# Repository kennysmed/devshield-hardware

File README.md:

devshield-hardware
==================

Schematics and Eagle files for the BERG Cloud Dev Shield.

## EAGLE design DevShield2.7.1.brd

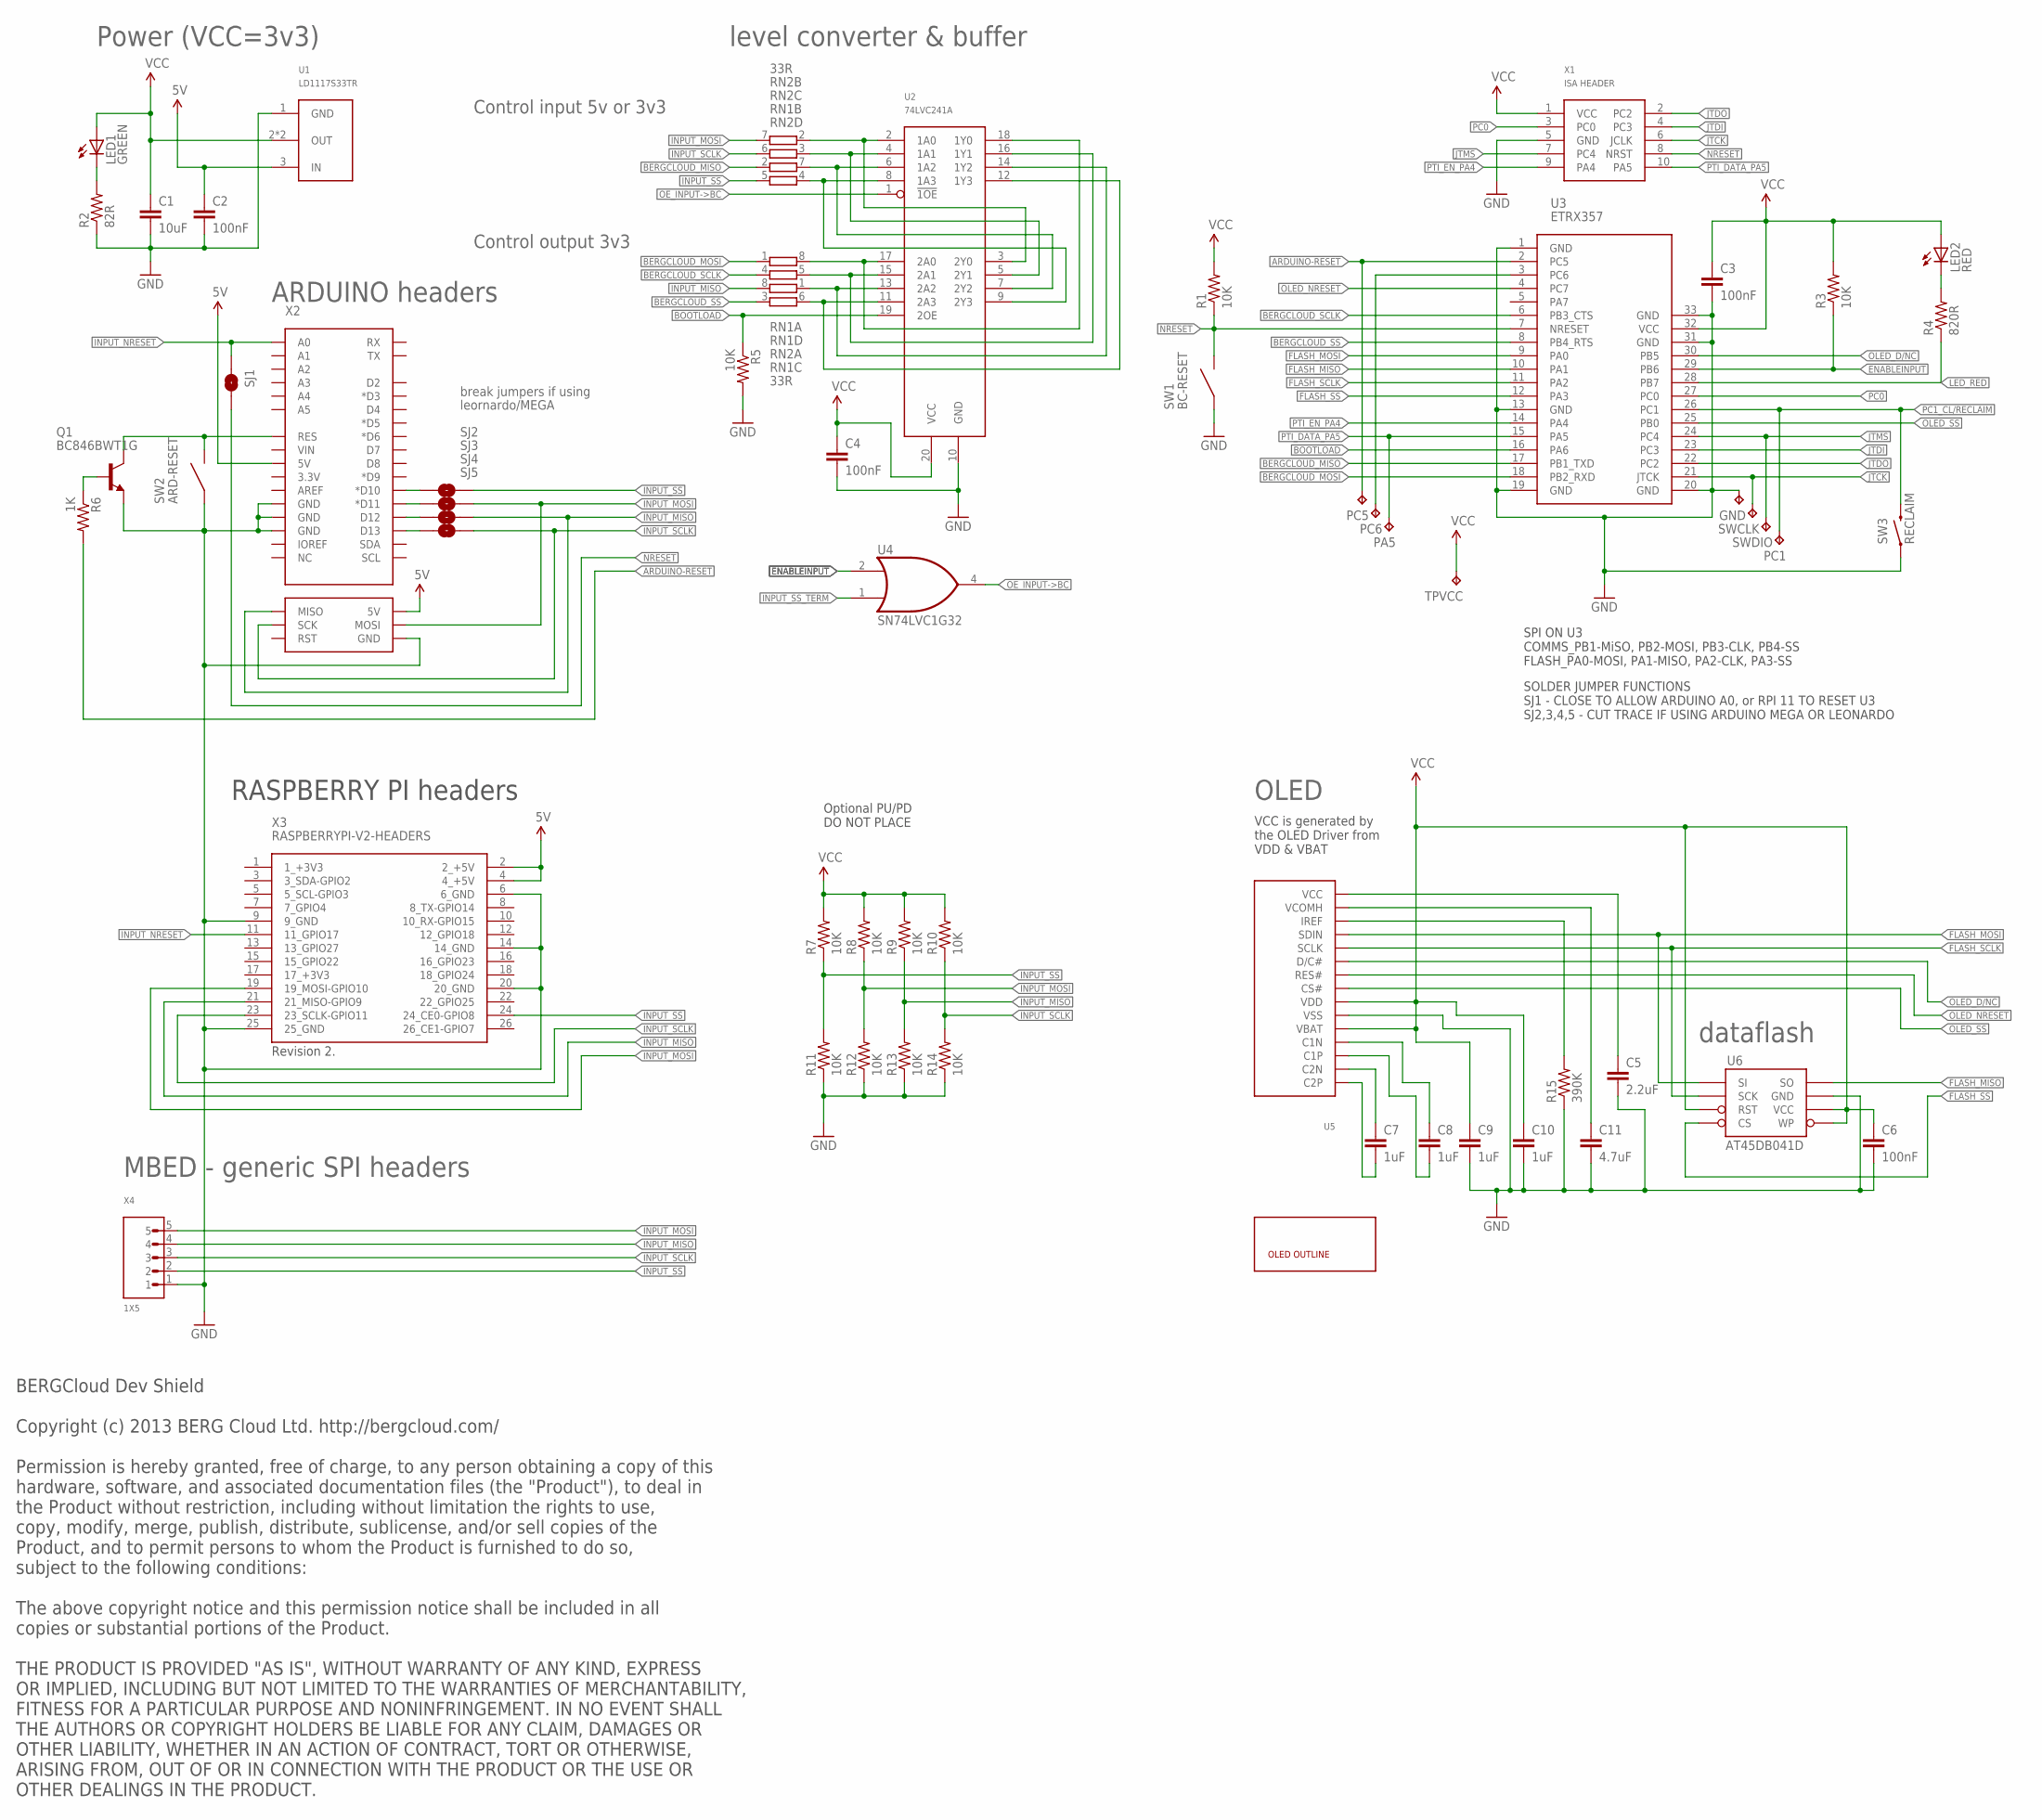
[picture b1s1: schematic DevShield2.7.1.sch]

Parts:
C1: 10uF; C0805K; MPN 06033C104KAZ2A
C2, C3, C4, C6: 100nF; C0603K; MPN 06033C104KAZ2A
C5: 2.2uF; 0603-CAP; MPN 06036D225KAT2A
C7, C8, C9, C10: 1uF; 0603-CAP; MPN 02016D105MAT2A
C11: 4.7uF; 0805; MPN 0805ZD475KAT2A
GND: TPTP15R; TP15R
IGNORE: ER-OLED0.91-1-OUTLINE; ER-OLED0.91-SCREEN
LED1: GREEN; CHIPLED_0603; MPN ASMT-RH45-AQ502
LED2: RED; CHIPLED_0603; MPN ASMT-RH45-AQ502
PA5: TPTP15R; TP15R
PC1, PC5, PC6: TPTP15R; TP15R
Q1: BC846BWT1G; SOT323; MPN BC846BWT1G
R1, R3, R5, R7, R8, R9, R10, R11, R12, R13, R14: 10K; 0603-RES
R2: 82R; 0603-RES
R4: 820R; 0603-RES
R6: 1K; 0603-RES; MPN MC0063W060311K
R15: 390K; 0603-RES; MPN ERJU03F3903V
RN1, RN2: 33R; CAT16
SJ1: SOLDERJUMPERNO; SJ_2S-NO
SJ2, SJ3, SJ4, SJ5: SOLDERJUMPERTRACE; SJ_2S-TRACE
SW1: BC-RESET; TE_FSMSM; MPN FSMSM
SW2: ARD-RESET; TE_FSMSM; MPN FSMSM
SW3: RECLAIM; TACTILE_SWITCH_SMD
SWCLK: TPTP15R; TP15R
SWDIO: TPTP15R; TP15R
TPVCC: TPTP15R; TP15R
U1: LD1117S33TR; SOT223
U2: 74LVC241A; TSSOP20
U3: ETRX357; ETRX35XSMD
U4: SN74LVC1G32; SC70-5; MPN SN74LVC1G32DCKR
U5: ER-OLED0.91-1HANDSOLDER_BOTTOMLAYER; FPC15WAYOLED
U6: AT45DB041D; SO08; MPN AT45DB041D-SSU
X1: ISA HEADER; SHF-105-01-L-D-SM
X2: ARDUINO_UNO_IO_INCL_ICSP; ARDUINO_UNO_ICSP
X3: RASPBERRYPI-V2-HEADERS; 13X2_2.54MM
X4: 1X5; 1X05

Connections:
5V: C2.1, U1.3 (IN), X2.5V@0 (5V), X2.ICSP_5V (5V), X3.2 (2_+5V), X3.4 (4_+5V)
ARDUINO-RESET: PC5.TP, R6.2, U3.2 (PC5)
ARD_RESET_5V: Q1.3 (C), SW2.P$1, X2.RES
BERGCLOUD_MISO: RN1.2 (1), U3.17 (PB1_TXD)
BERGCLOUD_MISO_TERM: RN1.7 (2), U2.6 (1A2), U2.7 (2Y2)
BERGCLOUD_MOSI: RN1.1, U3.18 (PB2_RXD)
BERGCLOUD_MOSI_TERM: RN1.8 (2), U2.17 (2A0), U2.18 (1Y0)
BERGCLOUD_SCLK: RN1.4 (1), U3.6 (PB3_CTS)
BERGCLOUD_SCLK_TERM: RN1.5 (2), U2.15 (2A1), U2.16 (1Y1)
BERGCLOUD_SS: RN1.3 (1), U3.8 (PB4_RTS)
BERGCLOUD_SS_TERM: RN1.6 (2), U2.11 (2A3), U2.12 (1Y3)
BOOTLOAD: R5.1, U2.19 (2OE), U3.16 (PA6)
ENABLEINPUT: R3.1, U3.29 (PB6), U4.2 (I0)
FLASH_MISO: U3.10 (PA1), U6.8 (SO)
FLASH_MOSI: U3.9 (PA0), U5.P$12 (SDIN), U6.1 (SI)
FLASH_SCLK: U3.11 (PA2), U5.P$11 (SCLK), U6.2 (SCK)
FLASH_SS: U3.12 (PA3), U6.4 (CS)
GND: C1.2, C2.2, C3.2, C4.2, C5.2, C6.2, C9.2, C10.2, C11.2, GND.TP, Q1.2 (E), R2.1, R5.2, R11.1, R12.1, R13.1, R14.1, R15.1, SW1.P$2, SW2.P$2, SW3.1, U1.1 (GND), U2.10 (GND), U3.1 (GND), U3.13 (GND), U3.19 (GND), U3.20 (GND), U3.31 (GND), U3.33 (GND), U4.3 (GND), U5.P$6 (VSS), U6.7 (GND), X1.5 (GND), X2.GND@0 (GND), X2.GND@1 (GND), X2.GND@2 (GND), X2.GND@03 (GND), X3.6 (6_GND), X3.9 (9_GND), X3.14 (14_GND), X3.20 (20_GND), X3.25 (25_GND), X4.1
INPUT_MISO: R9.1, R13.2, RN2.8 (2), SJ4.2, X2.ICSP_MISO (MISO), X3.21 (21_MISO-GPIO9), X4.4
INPUT_MISO_TERM: RN2.1, U2.13 (2A2), U2.14 (1Y2)
INPUT_MOSI: R8.1, R12.2, RN2.7 (2), SJ3.2, X2.ICSP_MOSI (MOSI), X3.19 (19_MOSI-GPIO10), X4.5
INPUT_MOSI_TERM: RN2.2 (1), U2.2 (1A0), U2.3 (2Y0)
INPUT_NRESET: SJ1.1, X2.A0, X3.11 (11_GPIO17)
INPUT_SCLK: R10.1, R14.2, RN2.6 (2), SJ5.2, X2.ICSP_SCK (SCK), X3.23 (23_SCLK-GPIO11), X4.3
INPUT_SCLK_TERM: RN2.3 (1), U2.4 (1A1), U2.5 (2Y1)
INPUT_SS: R7.1, R11.2, RN2.5 (2), SJ2.2, X3.24 (24_CE0-GPIO8), X4.2
INPUT_SS_TERM: RN2.4 (1), U2.8 (1A3), U2.9 (2Y3), U4.1 (I1)
JTCK: SWCLK.TP, U3.21 (JTCK), X1.6 (JCLK)
JTDI: U3.23 (PC3), X1.4 (PC3)
JTDO: U3.22 (PC2), X1.2 (PC2)
JTMS: SWDIO.TP, U3.24 (PC4), X1.7 (PC4)
LED_RED: R4.1, U3.28 (PB7)
unnamed: LED1.C, R2.2
unnamed: SJ2.1, X2.D10 (*D10)
unnamed: SJ3.1, X2.D11 (*D11)
unnamed: SJ4.1, X2.D12
unnamed: SJ5.1, X2.D13
unnamed: C7.1, U5.P$2 (C2N)
unnamed: C7.2, U5.P$1 (C2P)
unnamed: C8.2, U5.P$3 (C1P)
unnamed: LED2.C, R4.2
unnamed: C8.1, U5.P$4 (C1N)
unnamed: C5.1, U5.P$15 (VCC)
unnamed: C11.1, U5.P$14 (VCOMH)
unnamed: R15.2, U5.P$13 (IREF)
unnamed: Q1.1 (B), R6.1
NRESET: R1.1, SJ1.2, SW1.P$1, U3.7 (NRESET), X1.8 (NRST)
OE_INPUT->BC: U2.1 (!1OE), U4.4 (O)
OLED_D/NC: U3.30 (PB5), U5.P$10 (D/C#)
OLED_NRESET: U3.4 (PC7), U5.P$9 (RES#)
OLED_SS: U3.25 (PB0), U5.P$8 (CS#)
PC0: U3.27 (PC0), X1.3 (PC0)
PC1_CL/RECLAIM: PC1.TP, SW3.3 (2), U3.26 (PC1)
PC6: PC6.TP, U3.3 (PC6)
PTI_DATA_PA5: PA5.TP, U3.15 (PA5), X1.10 (PA5)
PTI_EN_PA4: U3.14 (PA4), X1.9 (PA4)
VCC: C1.1, C3.1, C4.1, C6.1, C9.1, C10.1, LED1.A, LED2.A, R1.2, R3.2, R7.2, R8.2, R9.2, R10.2, TPVCC.TP, U1.2 (OUT), U1.4 (OUT), U2.20 (VCC), U3.32 (VCC), U4.5 (VCC), U5.P$5 (VBAT), U5.P$7 (VDD), U6.3 (RST), U6.5 (WP), U6.6 (VCC), X1.1 (VCC)

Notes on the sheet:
RASPBERRY PI headers
Control input 5v or 3v3
Control output 3v3
ARDUINO headers
level converter & buffer
break jumpers if using
MBED - generic SPI headers
Power (VCC=3v3)
leornardo/MEGA
dataflash
OLED
VCC is generated by the OLED Driver from VDD & VBAT
SPI ON U3 COMMS_PB1-MiSO, PB2-MOSI, PB3-CLK, PB4-SS FLASH_PA0-MOSI, PA1-MISO, PA2-CLK, PA3-SS
SOLDER JUMPER FUNCTIONS SJ1 - CLOSE TO ALLOW ARDUINO A0, or RPI 11 TO RESET U3 SJ2,3,4,5 - CUT TRACE IF USING ARDUINO MEGA OR LEONARDO
Optional PU/PD DO NOT PLACE
BERGCloud Dev Shield Copyright (c) 2013 BERG Cloud Ltd. http://bergcloud.com/ Permission is hereby granted, free of charge, to any person obtaining a copy of this hardware, software, and associated documentation files (the "Product"), to deal in the Product without restriction, including without li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

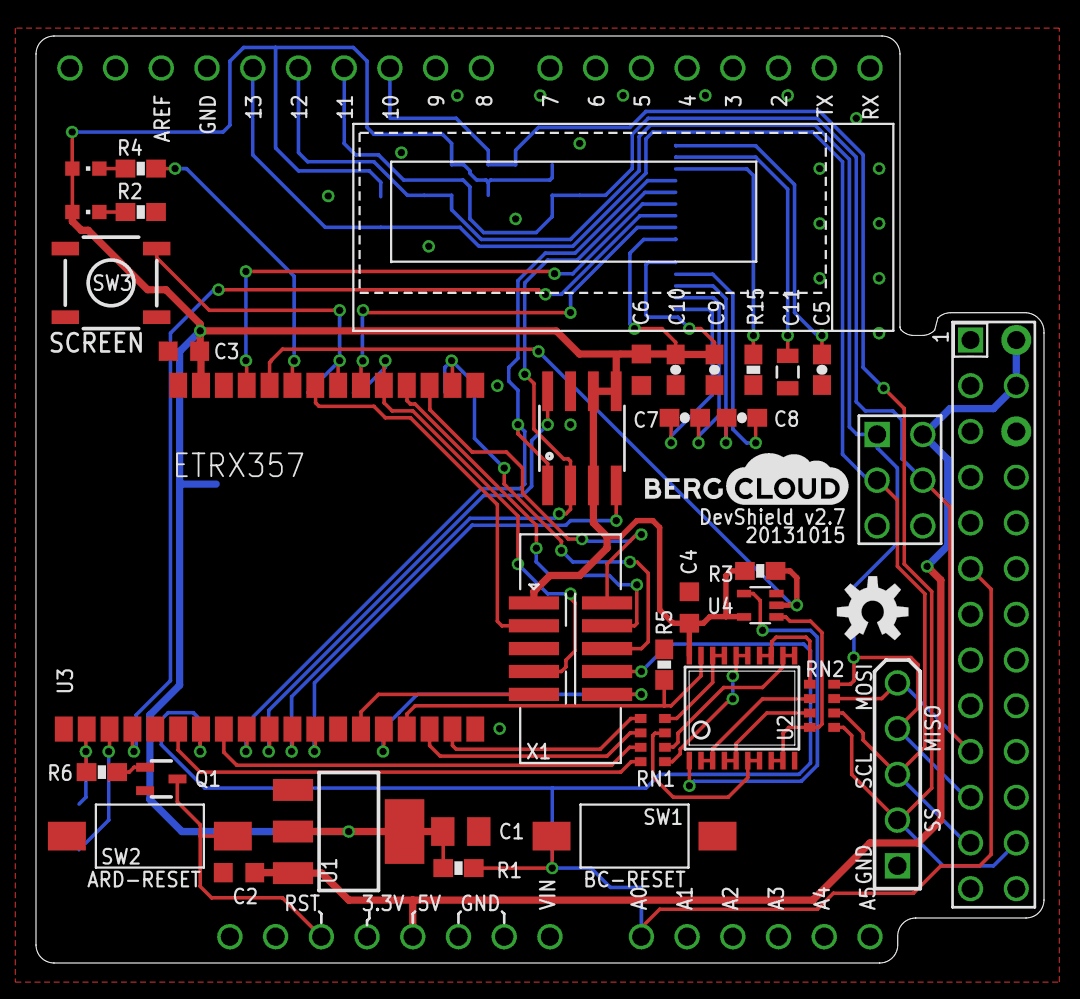
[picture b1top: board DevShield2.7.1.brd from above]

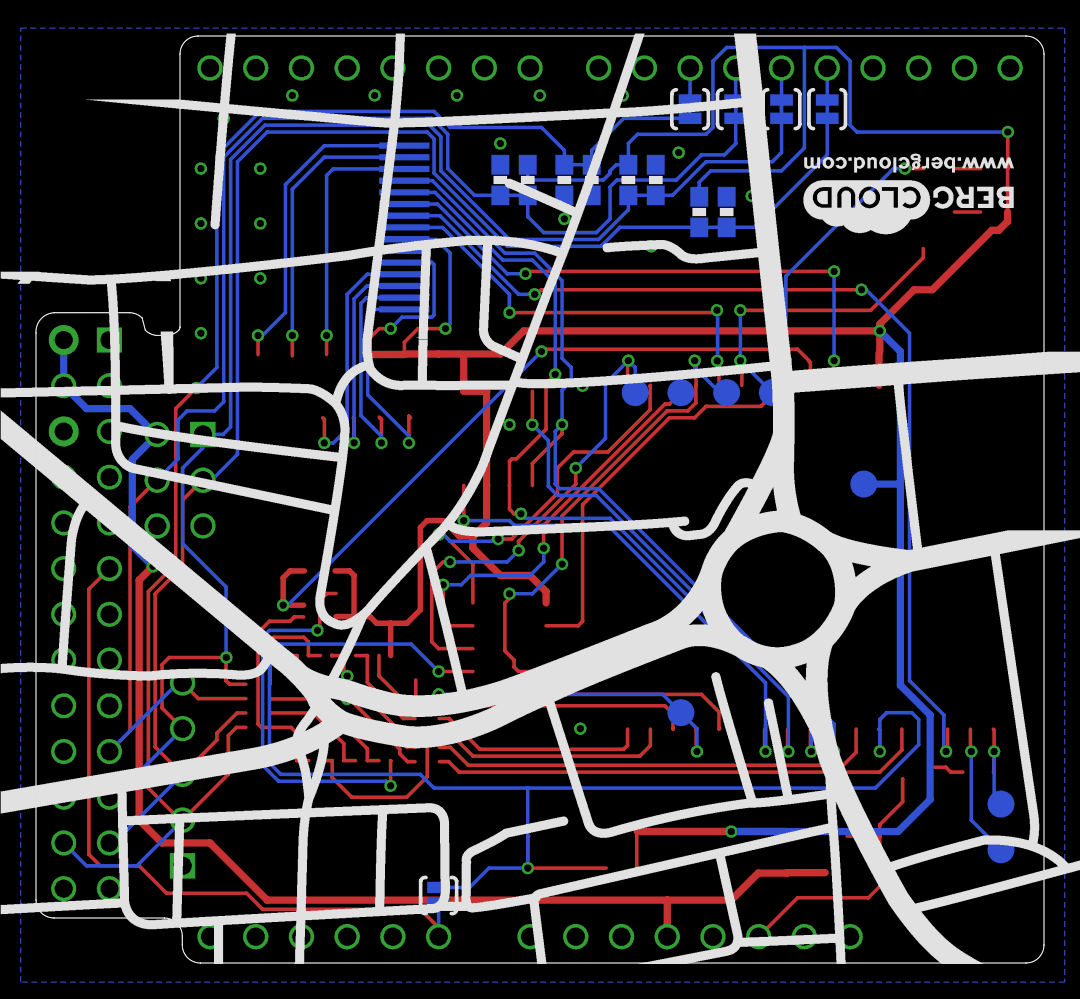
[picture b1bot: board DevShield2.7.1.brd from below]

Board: 2 copper layers, 56.0 x 51.5 mm, 58 parts (22 on the bottom side), 57 nets.

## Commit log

2013-10-24 Update LICENSE
    "Product" instead of "Software"
2013-10-24 Adding Eagle 6 .brd and .sch files.
2013-10-24 house keeping, .gitignore
2013-10-29 Added the BERG Cloud component library.
2013-11-12 Added .pdf schematic
2013-11-12 Updated Library and pin names for Raspberry Pi
2013-11-12 fixed airwire

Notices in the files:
parts and their libraries:
BERGCloud-OSH: These are provided for convenience and any use should be double checked before production. Just to be clear:
The MIT License (MIT)
